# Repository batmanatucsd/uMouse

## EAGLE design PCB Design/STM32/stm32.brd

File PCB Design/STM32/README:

VCC = 3.3v
VDDA = 3.3V
V_BATT = battery voltage

AVOID:
there is a temperature sensor at ADC1_IN16

PC13,14,15 less output current

review the direction of motor connector in board design

CIN for NCP1117 -- 10uf (typ)
Cout for NCP1117 > 4.7uf (ESR) that is within the limits of 33 m (typ) to 2.2  is required.

*******************************************************************************
*******************************************************************************

Default boot from bank 1(512K)

Bootloader: activate by apply Pattern3
BOOT0--GND
BOOT1--GND
BFB2--in the user option memory

/*****************************************************************************/
// USART
/*****************************************************************************/
USART1 be used in simple debug situation
PA9--USART1_TX
PA10--USART1_RX

PA8--USART1_CK
PA11--USART1_CTS
PA12--USART1_RTS

/*****************************************************************************/
// JTAG
/*****************************************************************************/
CONNECT to JTAG(for advance debug)
NRST--RST
PA13--JT_TMS
PA14--JT_TCK
PA15--JT_TDI
PB3--JT_TDO
PB4--JT_TRST

/*****************************************************************************/
// Gyro
/*****************************************************************************/
PB5--I2C1_SMBA
PC12--INT
PB8--I2C1_SCL--REMAP
PB9--I2C1_SDA--REMAP

/*****************************************************************************/
// Motor Driver
/*****************************************************************************/
PA4--STBY

// RIGHT
PA1--M1PWM (TIM5_CH2 or TIM2_CH2)
PA3--M1I1
PA2--M1I2

// LEFT
PA7--M2PWM (TIM3_CH2 or TIM8_CH1N or TIM14_CH1)
PA5--M2I1
PA6--M2I2

/*****************************************************************************/
// Encoder
/*****************************************************************************/
// RIGHT
PB6--M1CA (TIM4_CH1)
PB7--M1CB (TIM4_CH2)

// LEFT
PC7--M2CA (TIM3_CH2) // need to remap
PC6--M2CB (TIM3_CH1)

might be able to just use TIM8 instead of TIM3

/*****************************************************************************/
// IR Sensor
/*****************************************************************************/
// From left to right
PC0--IR_IN1 (ADC123_IN10)
PC1--IR_IN2 (ADC123_IN11)
PC2--IR_IN3 (ADC123_IN12)
PC3--IR_IN4 (ADC123_IN13)

PB15--IR_OUT1
PB14--IR_OUT2
PB13--IR_OUT3
PB12--IR_OUT4

/*****************************************************************************/
// Indicator
/*****************************************************************************/
PB10--BUTTON1
PC4--LED1 - green
PC5--LED2 - yellow
PB0--LED3 - red

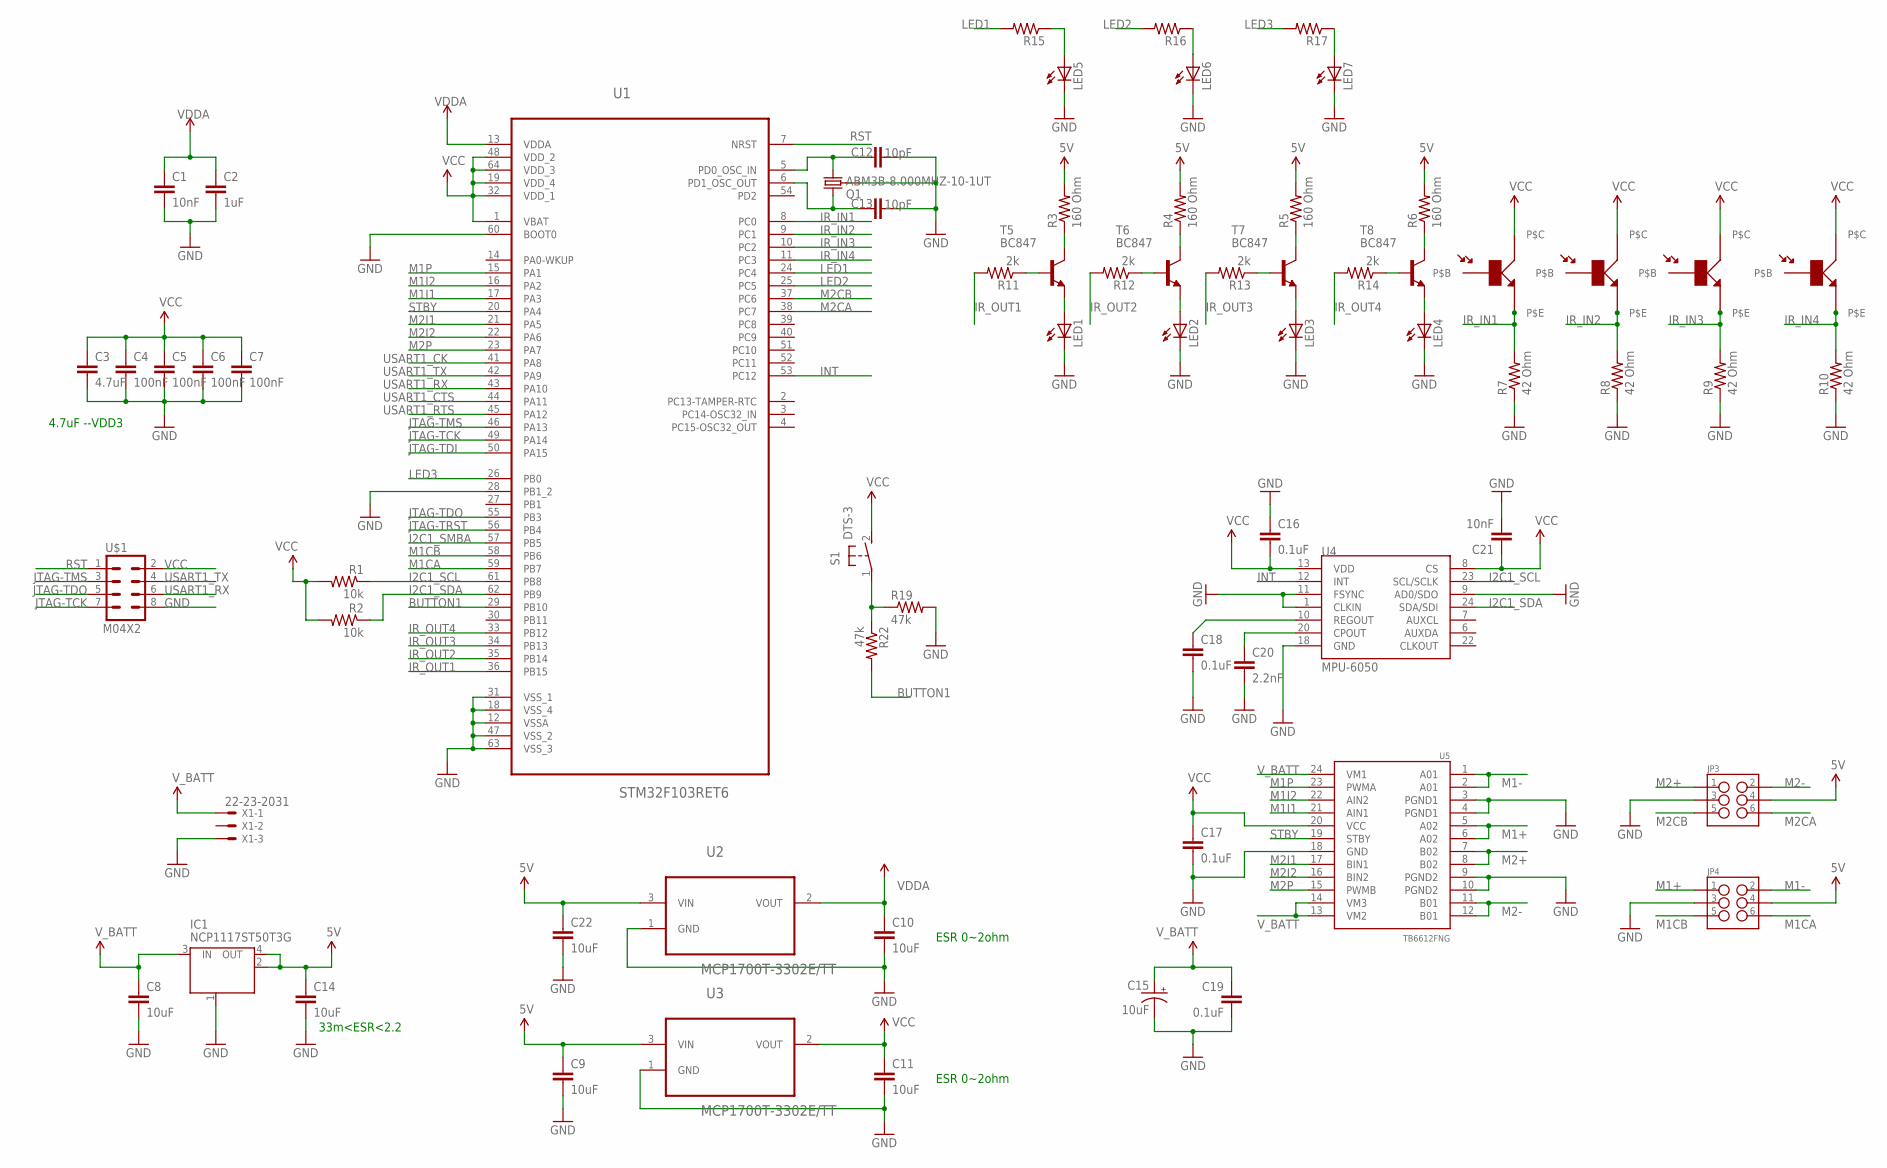
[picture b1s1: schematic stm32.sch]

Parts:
C1, C21: 10nF; 0805
C2: 1uF; 0805
C3: 4.7uF; 0805
C4, C5, C6, C7: 100nF; 0805
C8, C9, C10, C11, C14, C22: 10uF; 0805
C12, C13: 10pF; 0805
C15: 10uF; EIA3216-KIT
C16, C17, C18, C19: 0.1uF; 0805
C20: 2.2nF; 0805
IC1: NCP1117ST50T3G; SOT223
JP3, JP4: M03X2NO_SILK; 2X3-NS
LED1, LED2, LED3, LED4: LED5MM
LED5, LED6, LED7: LEDSML0805; SML0805
Q1: ABM3B-8.000MHZ-10-1UT; CRYSTAL-SMD-5X3
R1, R2: 10k; 0805
R3, R4, R5, R6: 160 Ohm; 0805
R7, R8, R9, R10: 42 Ohm; 0805
R11, R12, R13, R14: 2k; 0805
R15, R16, R17: RESISTOR0805-RES; 0805
R19, R22: 47k; 0805
S1: DTS-3
T5, T6, T7, T8: BC847; SOT23
U1: STM32F103RET6; QFP50P1200X1200X160-64N
U2, U3: MCP1700T-3302E/TT; SOT95P237X112-3N
U4: MPU-6050; QFN-24-TESTING
U5: TB6612FNG; SSOP24
U$1: M04X2; 2X4
U$2, U$3, U$4, U$5: PHTRST
X1: 22-23-2031

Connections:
5V: C9.1, C14.1, C22.1, IC1.2 (OUT), IC1.4 (OUT), JP3.4, JP4.4, R3.2, R4.2, R5.2, R6.2, U2.3 (VIN), U3.3 (VIN)
BUTTON1: R22.2, U1.29 (PB10)
GND: C1.2, C2.2, C3.2, C4.2, C5.2, C6.2, C7.2, C8.2, C9.2, C10.2, C11.2, C12.1, C13.1, C14.2, C15.C (-), C16.1, C17.2, C18.2, C19.2, C20.2, C21.2, C22.2, IC1.1 (GND/ADJ), JP3.3, JP4.3, LED1.K (C), LED2.K (C), LED3.K (C), LED4.K (C), LED5.C, LED6.C, LED7.C, Q1.2 (3), Q1.4 (3), R7.1, R8.1, R9.1, R10.1, R19.2, U1.12 (VSSA), U1.18 (VSS_4), U1.28 (PB1_2), U1.31 (VSS_1), U1.47 (VSS_2), U1.60 (BOOT0), U1.63 (VSS_3), U2.1 (GND), U3.1 (GND), U4.1 (CLKIN), U4.9 (AD0/SDO), U4.11 (FSYNC), U4.18 (GND), U5.3 (PGND1), U5.4 (PGND1), U5.9 (PGND2), U5.10 (PGND2), U5.18 (GND), U$1.8, X1.3
I2C1_SCL: R1.1, U1.61 (PB8), U4.23 (SCL/SCLK)
I2C1_SDA: R2.1, U1.62 (PB9), U4.24 (SDA/SDI)
I2C1_SMBA: U1.57 (PB5)
INT: U1.53 (PC12), U4.12 (INT)
IR_IN1: R7.2, U1.8 (PC0), U$2.P$E
IR_IN2: R8.2, U1.9 (PC1), U$3.P$E
IR_IN3: R9.2, U1.10 (PC2), U$4.P$E
IR_IN4: R10.2, U1.11 (PC3), U$5.P$E
IR_OUT1: R11.2, U1.36 (PB15)
IR_OUT2: R12.2, U1.35 (PB14)
IR_OUT3: R13.2, U1.34 (PB13)
IR_OUT4: R14.2, U1.33 (PB12)
JTAG-TCK: U1.49 (PA14), U$1.7
JTAG-TDI: U1.50 (PA15)
JTAG-TDO: U1.55 (PB3), U$1.5
JTAG-TMS: U1.46 (PA13), U$1.3
JTAG-TRST: U1.56 (PB4)
LED1: R15.2, U1.24 (PC4)
LED2: R16.2, U1.25 (PC5)
LED3: R17.2, U1.26 (PB0)
M1+: JP4.1, U5.5 (A02), U5.6 (A02)
M1-: JP4.2, U5.1 (A01), U5.2 (A01)
M1CA: JP4.6, U1.59 (PB7)
M1CB: JP4.5, U1.58 (PB6)
M1I1: U1.17 (PA3), U5.21 (AIN1)
M1I2: U1.16 (PA2), U5.22 (AIN2)
M1P: U1.15 (PA1), U5.23 (PWMA)
M2+: JP3.1, U5.7 (B02), U5.8 (B02)
M2-: JP3.2, U5.11 (B01), U5.12 (B01)
M2CA: JP3.6, U1.38 (PC7)
M2CB: JP3.5, U1.37 (PC6)
M2I1: U1.21 (PA5), U5.17 (BIN1)
M2I2: U1.22 (PA6), U5.16 (BIN2)
M2P: U1.23 (PA7), U5.15 (PWMB)
unnamed: C12.2, Q1.3 (1), U1.5 (PD0_OSC_IN)
unnamed: R4.1, T6.3 (C)
unnamed: LED1.A, T5.2 (E)
unnamed: LED2.A, T6.2 (E)
unnamed: C13.2, Q1.1 (2), U1.6 (PD1_OSC_OUT)
unnamed: LED3.A, T7.2 (E)
unnamed: C20.1, U4.20 (CPOUT)
unnamed: C18.1, U4.10 (REGOUT)
unnamed: LED4.A, T8.2 (E)
unnamed: R3.1, T5.3 (C)
unnamed: R5.1, T7.3 (C)
unnamed: R6.1, T8.3 (C)
unnamed: R14.1, T8.1 (B)
unnamed: R13.1, T7.1 (B)
unnamed: R12.1, T6.1 (B)
unnamed: R11.1, T5.1 (B)
unnamed: LED5.A, R15.1
unnamed: LED6.A, R16.1
unnamed: LED7.A, R17.1
unnamed: R19.1, R22.1, S1.1
RST: U1.7 (NRST), U$1.1
STBY: U1.20 (PA4), U5.19 (STBY)
USART1_CK: U1.41 (PA8)
USART1_CTS: U1.44 (PA11)
USART1_RTS: U1.45 (PA12)
USART1_RX: U1.43 (PA10), U$1.6
USART1_TX: U1.42 (PA9), U$1.4
VCC: C3.1, C4.1, C5.1, C6.1, C7.1, C11.1, C16.2, C17.1, C21.1, R1.2, R2.2, S1.2, U1.1 (VBAT), U1.19 (VDD_4), U1.32 (VDD_1), U1.48 (VDD_2), U1.64 (VDD_3), U3.2 (VOUT), U4.8 (CS), U4.13 (VDD), U5.20 (VCC), U$1.2, U$2.P$C, U$3.P$C, U$4.P$C, U$5.P$C
VDD: C1.1, C2.1, C10.1, U1.13 (VDDA), U2.2 (VOUT)
V_BATT: C8.1, C15.A (+), C19.1, IC1.3 (IN), U5.13 (VM2), U5.14 (VM3), U5.24 (VM1), X1.1

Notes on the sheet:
ESR 0~2ohm
4.7uF --VDD3
33m<ESR<2.2

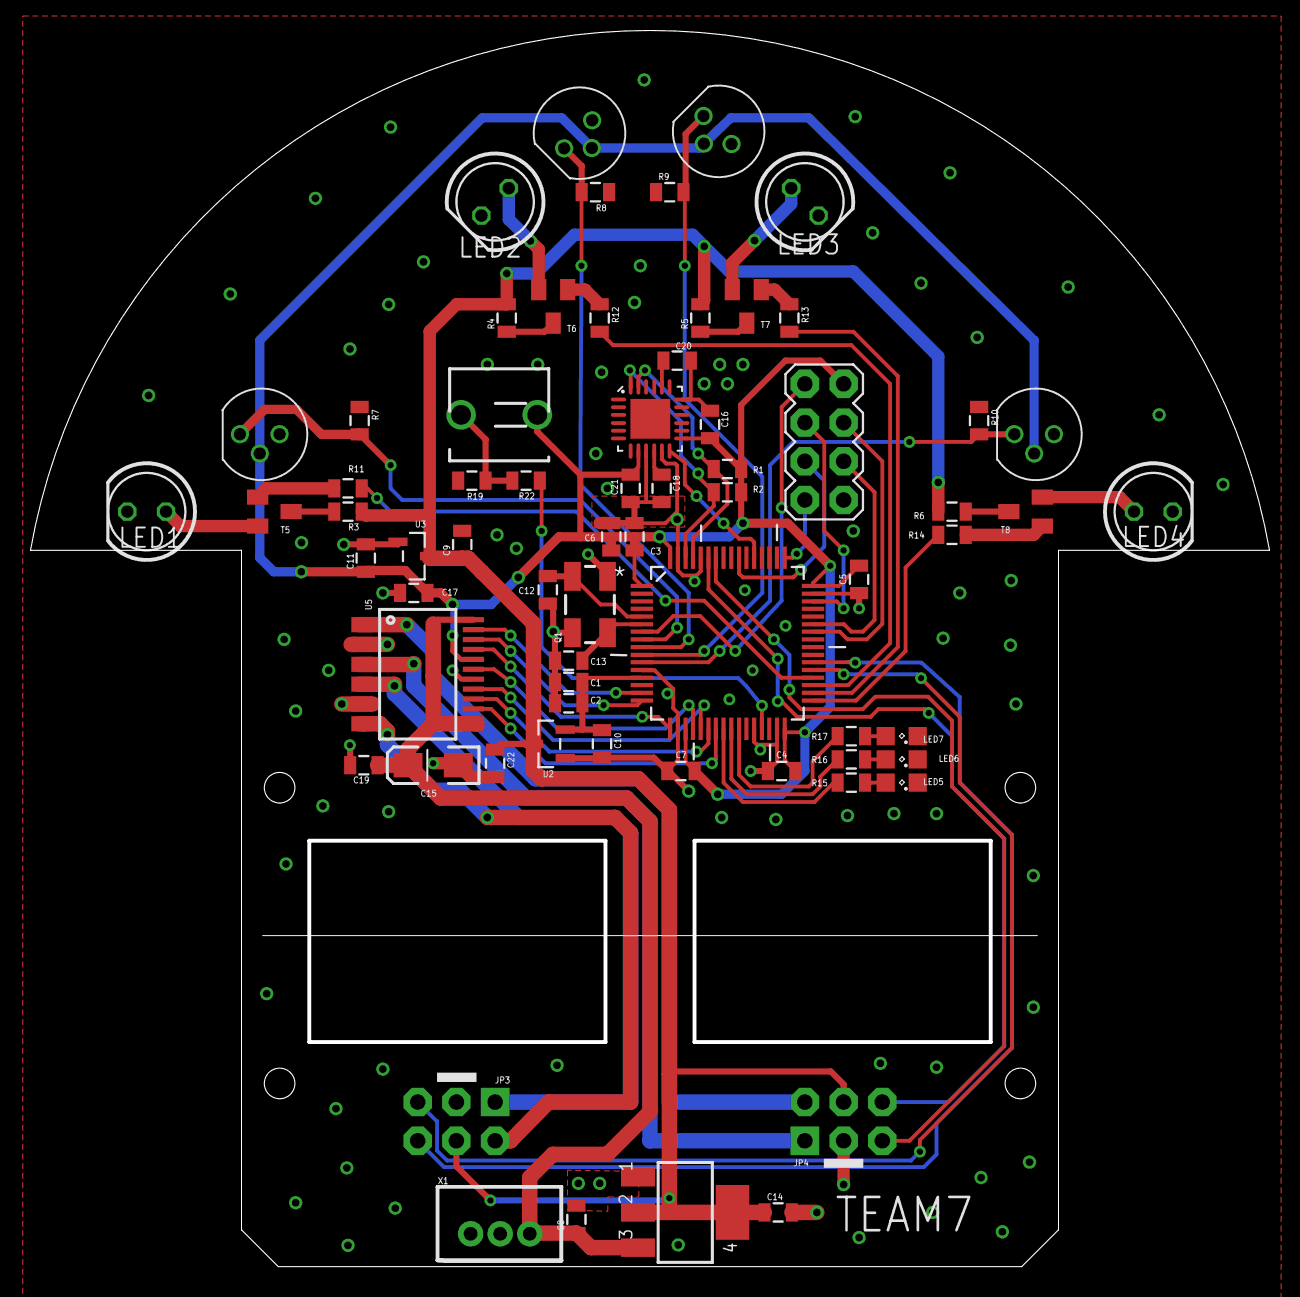
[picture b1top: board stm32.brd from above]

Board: 2 copper layers, 81.3 x 81.1 mm, 68 parts (0 on the bottom side), 61 nets.

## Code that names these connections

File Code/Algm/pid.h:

// Constants
// IR_OUT:
// 1 - left
// 2 - front left
// 3 - front right
// 4 - right

#define IR_OUT1 37
#define IR_OUT2 38
#define IR_OUT3 39
#define IR_OUT4 40
#define IR_IN1 8
#define IR_IN2 9
#define IR_IN3 10
#define IR_IN4 11

#define THRESHOLD 999
#define KP 999
#define KD 999
#define ADJUST 999

#ifndef HIGH
#define HIGH 1
#endif

#ifndef LOW
#define LOW 0
#endif

/*****************************************************************************/
// PID Globals
/*****************************************************************************/
float pastError=0, currentError=0, 
      leftIR=0, rightIR=0, 
      leftEncoder=0, rightEncoder=0, 
      leftSpeed=0, rightSpeed=0;

/*****************************************************************************/
// Functions
/*****************************************************************************/
void pid();

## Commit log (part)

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2014-11-25 gitignore for eagle cad
2014-11-27 memo init
2014-11-27 add the pin definition
2014-11-27 first design
2014-11-28 improvement
2014-12-04 it begins
2014-12-04 setup project
2014-12-06 mpu6050 update and small fix
    TODO: change the boot pin
2014-12-06 datasheet update
2014-12-06 TB6612 update & Boot selection removed
    TODO: review the power circuit in the design & connect motor to MCU
2014-12-06 tb6612 connect to MCU & design improve
2014-12-06 minor upgrade
2014-12-07 compiles
2014-12-08 Update README.md
    James Lee
2014-12-08 changed readme
2014-12-08 Alvin
2014-12-08 TK added her contact info to README
2014-12-08 alex changed this
2014-12-08 hello
2014-12-08 updated pid.c
2014-12-08 Readme updated
2014-12-10 start to prepare the toolchain
2014-12-10 README update
2014-12-10 first draft of makefile
2014-12-14 test makefile
2014-12-15 makefile first release
    please follow the instruction in /Code/README
2014-12-15 gitignore & optimize level update
2014-12-16 attach the stratup code to the compile
    my fault
2014-12-16 will switch to a modified version linker script for our chip
    copied from
    \Code\STM32F10x_StdPeriph_Lib_V3.5.0\Project\STM32F10x_StdPeriph_Template\TrueSTUDIO\STM3210E-EVAL_XL
2014-12-16 update linker script
2014-12-16 add a option to compile the project for discovery board
2014-12-16 refine readme
2014-12-18 discovery board dataasheet
2014-12-18 confirm bug in the building system
2014-12-20 bug solve & basic building system is done
    the bug comes from the optimization of GCC; gcc will automatically
    ignore a empty loop which is essential for a delay loop.
2014-12-20 update the optimization level for the embedded system
2014-12-21 reintroduce file
2014-12-22 testing
2014-12-23 the build system no longer compile the file not need into the binary file
2014-12-24 minor update
2014-12-24 update pid and schematic
2014-12-24 attach the i2c header file
2014-12-24 rename the file
2014-12-25 basic usart function
2014-12-25 init floodfill
2014-12-25 remove MAC file
2014-12-25 floodfill in progress
2014-12-25 print maze
2014-12-25 print direction and visited
2014-12-25 update in progress
2014-12-29 update()
2014-12-29 factor mcu codes
2014-12-29 refactored mcu functions
2014-12-29 rearrange the files & the makefile is destoryed right now
2014-12-29 testing main.c
2014-12-30 code search is done
2014-12-30 temporary fix
    TODO: redirect the output file
2014-12-31 makefile fixed
    the binary file is not redirected into the build folder
2014-12-31 little bug fix
2014-12-31 little bug fix 2
2014-12-31 datasheet update 3.1>3.4
2014-12-31 little bug fix 3
2014-12-31 the system now search for every c file under src folder
2014-12-31 enable the clock right before use to reduce confusion
2014-12-31 circuit remake
2014-12-31 board making
2014-12-31 added framework for wall reading
2015-01-01 board update
2015-01-01 started coding for PWM
2015-01-04 need gyro code asap
2015-01-05 errata sheet update
2015-01-05 add the dma library for i2c and adc & more study needed
2015-01-06 add 5v regulator
2015-01-06 refine connection
2015-01-07 i2c read test successful (On ADXL345)
2015-01-11 code looks nice
2015-01-11 stack conditions
2015-01-11 meeting update
2015-01-12 Code is commented
2015-01-12 commented
2015-01-12 Long wall test case successful
2015-01-12 stack works with long wall
2015-01-12 added indicating leds
2015-01-14 moved test cases to new branch
2015-01-14 first test case
2015-01-14 added toggle switch to schematic
2015-01-15 meet update 1
2015-01-16 meet update 3
2015-01-16 meet update 4
2015-01-16 meet update 5
2015-01-16 meet update 6
2015-01-17 added eagle library files
2015-01-17 meet update 7
2015-01-17 sleep save
2015-01-17 update8
2015-01-17 meal save
2015-01-18 FinalWheel and MotorMount
2015-01-18 first darft
2015-01-18 move folder
2015-01-19 update according to the change
2015-01-19 third draft
2015-01-19 crystal update
2015-01-22 changed to new phototransistors
2015-01-24 updated power to phototransistors and encoders
2015-01-24 updated power to phototransistors and the encoders
2015-01-24 added some comments in the main function
2015-01-24 save
2015-01-24 commented some things in floodfill.h
2015-01-24 oops that last one probably wouldnt' have compiled... fixed header file
2015-01-24 With pauses between each output
2015-01-24 Added a pause between each outpu
2015-01-24 debug stack
2015-01-24 Added pause for last output
2015-01-24 sleep
2015-01-24 created a really shitty testmaze thing for now, pretty much just duplicate code LMAO omg :(
2015-01-24 added DRU and CAM files for pcb design
2015-01-24 removed test case
2015-01-24 testmaze.c removed, everything will be set up in testmaze.h
2015-01-24 testmaze variable fixed
2015-01-24 rename board to maze
2015-01-24 rm exe
2015-01-24 optimize setup 4 walls
2015-01-24 testmaze variables fixed... for real this tiem
2015-01-24 mpushign testmaze to floodfil branch
2015-01-24 moving to floodfill branch
2015-01-24 moving to floodfill
2015-01-24 ok don't touch this code
2015-01-24 removed some final wheel files
2015-01-24 removed MotorMount.dwg
2015-01-24 finished final motormount and wheel
2015-01-24 removed old files from 3D folder
2015-01-25 final edition
2015-01-25 ultimate final edition
2015-01-25 gerber 1
2015-01-29 emergency update
2015-01-30 fixing the pcb
2015-01-30 finish update
2015-01-30 PCB README UPDATE
2015-02-12 Makefile to include testmaze stuff.
2015-02-15 IIC rename
2015-02-15 Move all i2c function outside of mcu_lib
2015-02-15 function update
2015-02-16 fix merge conflict with origin repo
2015-02-16 merging
2015-02-17 added a comment about bit masking in floodfill.h
2015-02-23 pushing onto personal branch
2015-02-24 okay test maze 1 is up and runniiiiinggg yaaaay
2015-02-25 removed trailing whitespaces
2015-03-11 iic rewrite 2
2015-03-12 read me update
2015-03-13 added dynamic PWM width change
2015-03-15 temporary save
2015-03-15 test1
2015-03-15 test2
2015-03-15 test3
2015-03-15 test 3
2015-03-16 test 4
2015-03-22 introduce the CPAL lib
2015-03-22 Revert "introduce the CPAL lib"
    This reverts commit c1320c635c22c08c64a197e95f5d622d84749881.
2015-03-25 erased all the mouse related code, bc this is discovery branch
2015-03-26 added mouse files and wrote pwm stuff
2015-03-26 added mouse files from master branch
2015-03-26 trying to test uart program
2015-03-26 compiled main in discovery branch
2015-03-26 testying uart program.. but failed
2015-03-26 added folds for vim
2015-03-26 trying to write uart write that sends int
2015-03-26 finished usart_sendint
2015-03-26 testing the ir sensors
2015-03-27 finished adc with software trigger
2015-03-29 update the make mode so that it is possible for debug
2015-03-30 added musart.h for enabling printf for debugging
2015-03-30 changed makefile so gdb is accessed easily
2015-03-31 forgot to add usart.c
2015-03-31 added files for interrupt handlers and wrote codes for injected conversions
2015-04-02 idk its kinda working ir sensors... it was better before...
2015-04-03 everything is stable when all the leds are turned on
2015-04-03 more stable ir sensors
2015-04-04 testmaze1 image added to go with testmaze1.txt
2015-04-04 adding move and lookAhead
2015-04-04 new branch floodfill
2015-04-04 testmaze.h fixed, but still not filling in the walls correctly... but at least it's fixed lol
2015-04-04 integrating testmaze
2015-04-04 lookahead 1/4 done
2015-04-04 1/4 working
2015-04-05 got the ir sensors working; working on the pid right now
2015-04-05 added pid stuff in the src folder
2015-04-05 added interrupt files
2015-04-05 still working on the pid
2015-04-05 pretty decent pid with two walls
2015-04-05 almost perfect pid, except for the no wall part
2015-04-10 included changes in mouse.c for stop and turns
2015-04-11 unecessary files deleted
2015-04-11 changes to mouse.c to include stop and turn
2015-04-12 working on turns
2015-04-12 added some macros for better programming
2015-04-16 made changes to include stop
2015-04-18 aalmost done with lookahead
2015-04-18 lookahead: only west cell left
2015-04-18 only west cell left forreals now
2015-04-18 floodfill
2015-04-18 floodfill.c east wall check fixed
2015-04-18 ok it infinite loops but correctly sees the walls
2015-04-18 floodfill.c
2015-04-19 trying new pid with linearization
2015-04-25 trying to fix stack issues with floodfill... some progress
2015-04-25 fixing floodfill, sees center wall and doesn't jump in
2015-04-25 merge
2015-04-25 separated turn and move functions
2015-04-25 fixing update
2015-05-09 mouse sees center wall, runs thru
2015-05-09 HOLY SHIT it works
2015-05-10 working on pid
2015-05-14 testing i2c 85% finish
2015-05-14 made changes to turn
2015-05-14 trying to work on the pid
2015-05-14 trying to fix sensor
2015-05-15 1st attempt at floodfillback
2015-05-15 works back and forth
2015-05-15 trying to merge with master and floodfill
2015-05-15 merging floodfill.c into master
2015-05-15 merging floodfill.h
2015-05-15 3 wall case
2015-05-15 three wall case
2015-05-16 trying to get 3 wall case to work.. not yet, and wont go back to start cell
2015-05-16 pretty good pid and turns
2015-05-16 working I2C commit
2015-05-16 makefile has change to make for mouse
2015-05-16 trying to update pid
2015-05-16 updating pid and floodfill
2015-05-16 refactored floodfill, removed lookAhead() bc it was confusing
2015-05-16 moved shit around
2015-05-16 fixed init
2015-05-16 readded init sig
2015-05-16 working on flooding values.....alkfj
2015-05-16 trying to merge floodfill
2015-05-16 still trying to put stopping and pid smoothly
2015-05-16 test 2 angle.c
2015-05-16 fixed backtrack bug
2015-05-16 what
2015-05-16 test angle 3
2015-05-16 reverting back to floodfill from 2 days ago
2015-05-17 re-flooding with values, all 255 and 0 in the middle works
2015-05-17 flooding
2015-05-17 before flooding
2015-05-17 setting visited
2015-05-17 test angle 4
2015-05-17 done
2015-05-17 whatevs
2015-05-17 added testmaze2
2015-05-17 second test maze
2015-05-17 removed .swp
2015-05-17 angle test 5
2015-05-17 todos added
2015-05-17 completegit add --all
2015-05-17 done in master
2015-05-17 update angle
2015-05-17 copy floodfill to src
2015-05-17 added motor controls
2015-05-17 working on calibration
2015-05-17 removed print statements from src
2015-05-17 simple angle update
2015-05-17 make flood fill compatible
2015-05-17 update simple angle algorithm
2015-05-17 trying to fix the sensor problem
2015-05-17 fixed the ADC problem
2015-05-17 test code update
2015-05-17 support C11
2015-05-17 pulling finished shit
2015-05-17 started working on integrating floodfill
2015-05-17 working on floodfill - commented somethings
2015-05-17 temporary stable
2015-05-17 successfully going back and foth with getWalls
2015-05-17 merger prepare
2015-05-17 testing hardware i2c
2015-05-17 prepare for compile
2015-05-17 prepare compile
2015-05-17 remove angle since not use it any more
2015-05-17 repeat function added
2015-05-17 fixed annoying ass brackets
2015-05-17 uncommenting forward and other functions from mouse.c in floodfill.c
2015-05-17 latest main.c
2015-08-30 move files around
2015-08-31 temp save
2015-08-31 will use readable file in the future
2015-09-01 libopencm3 transform
2015-09-01 more build file
2015-09-01 make bin as result
2015-09-01 verbose output
2015-09-01 new usart
2015-09-01 debug update
2015-09-01 remove mpu6050
2015-09-01 minor
2015-09-06 remove all anbt file
2015-09-06 rename
2015-09-06 reintroduce motion drive
2015-09-07 remove discovery datasheet
2015-09-08 markdown support
2015-09-08 disable interrupt during usart & refine libs
2015-09-08 better make & bug free delay
2015-09-08 refined delay
2015-09-08 functional eMPL
2015-09-08 mpu_configuration
2015-09-08 iic write
2015-09-08 functional iic_read
2015-09-08 more mpu function
2015-09-08 resolve strange math.h problem
2015-09-08 datasheet & comment update
2015-09-10 adc init
2015-09-10 partially markdown support
2015-09-10 move makefile around
2015-09-11 adc_update
2015-09-13 new adc is ready
    first request the data and do other things and you can get the data back
    later by read it.
2015-09-13 define function in adc
2015-09-13 move floodfill

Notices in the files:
parts and their libraries:
SparkFun-Capacitors: Licensing: Creative Commons ShareAlike 4.0 International - https://creativecommons.org/licenses/by-sa/4.0
